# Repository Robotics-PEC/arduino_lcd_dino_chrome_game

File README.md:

# Arduino lcd dinosaur chrome game

This Repository contains a simple attempt at replicating the famous dinosaur game of Chrome and running it on an arduino with an LCD and a push button.

# Sample Pictures

## DEMO 

## This is the first screen you would see when you startup the code.

## When you press the button given then the game stars running.

## When you press the button the dinosaur jumps up.

## If you don't jump in time then you crash into the tree and game over.

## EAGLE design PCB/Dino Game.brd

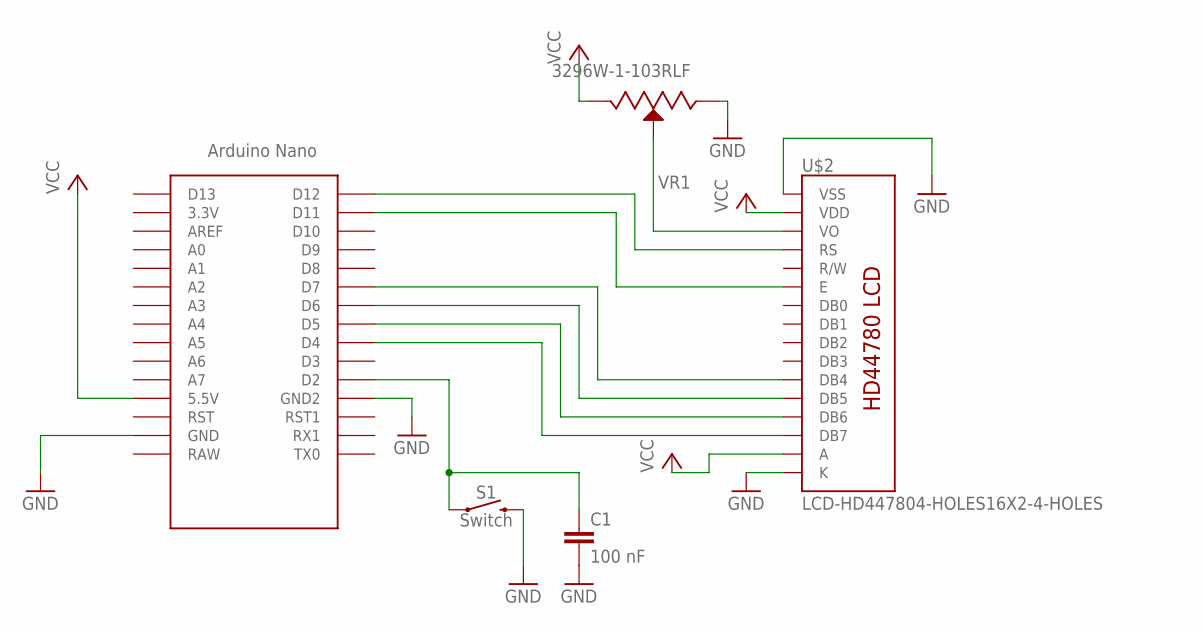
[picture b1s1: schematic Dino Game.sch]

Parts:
C1: 100 nF; C025-024X044
S1: Switch; TACTILE_SWITCH_PTH_12MM
U$1: NANO
U$2: LCD-HD447804-HOLES16X2-4-HOLES; LCD-16X2-4HOLES
VR1: 3296W-1-103RLF; TRIM_3296W-1-103RLF

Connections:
GND: C1.2, S1.3 (2), U$1.GND, U$1.GND1 (GND2), U$2.1 (VSS), U$2.16 (K), VR1.1 (CCW)
unnamed: U$1.D12, U$2.4 (RS)
unnamed: U$1.D11, U$2.6 (E)
unnamed: U$1.D7, U$2.11 (DB4)
unnamed: U$1.D6, U$2.12 (DB5)
unnamed: U$1.D5, U$2.13 (DB6)
unnamed: U$1.D4, U$2.14 (DB7)
unnamed: C1.1, S1.1, U$1.D2
unnamed: U$2.3 (VO), VR1.2 (WIPER)
VCC: U$1.5V (5.5V), U$2.2 (VDD), U$2.15 (A), VR1.3 (CW)

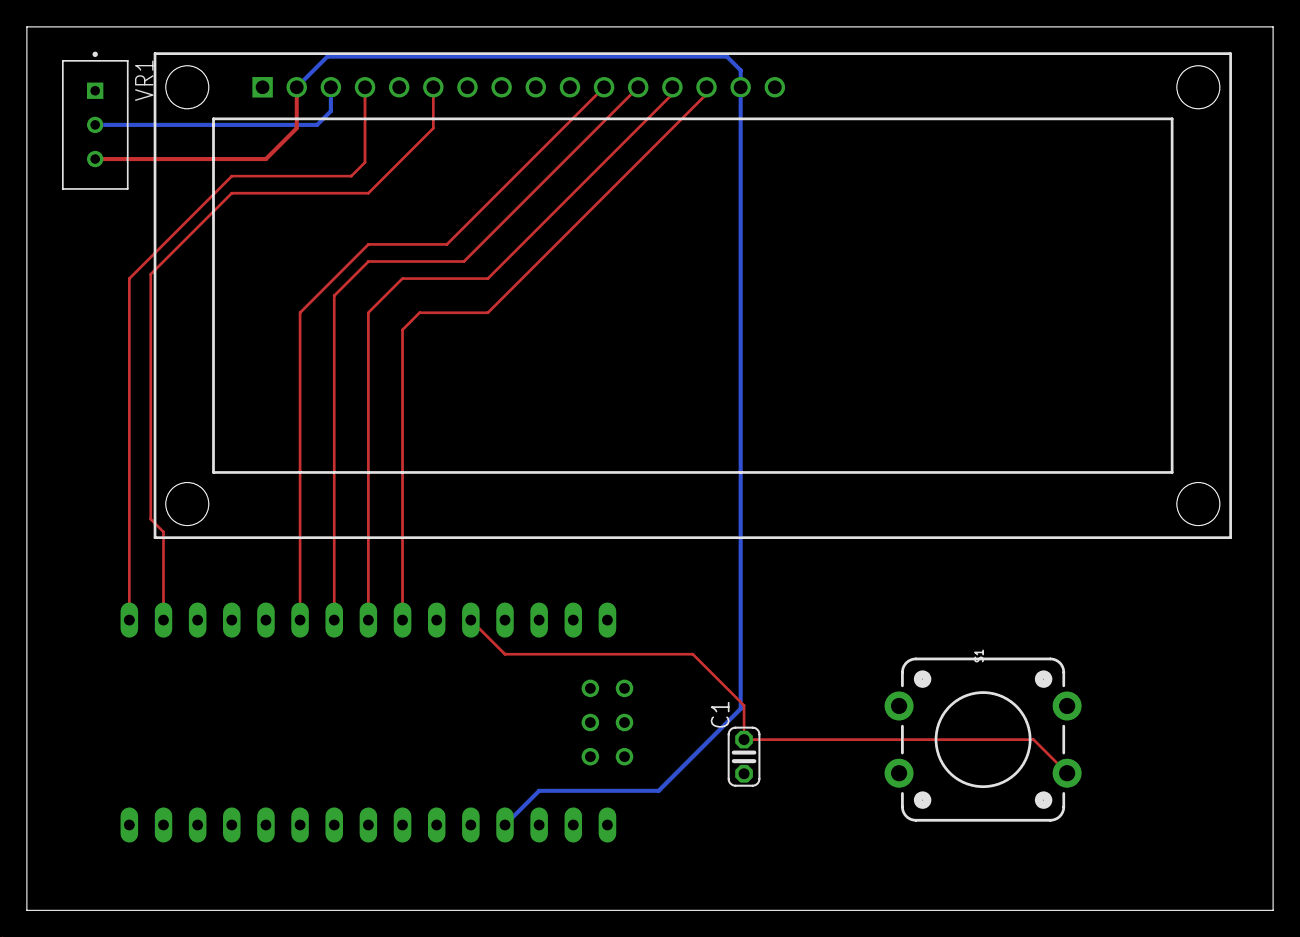
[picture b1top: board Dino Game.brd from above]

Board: 2 copper layers, 92.7 x 65.7 mm, 5 parts (0 on the bottom side), 10 nets.

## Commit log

2022-09-13 Added Readme
2022-09-13 Added Images and improved readme
2022-09-13 added animated gif to documentation
2022-09-16 Update lcd_dino_game.ino
    Added score counter and randomised the position of the tree
2022-09-18 animations
    added dino move animation and collision animation
2022-09-19 added movement animation
2022-09-22 added comments
2022-09-23 Updated comments
2022-09-25 Updated Photos
2022-10-25 added schematics and pcb files
2022-10-25 added gerber file

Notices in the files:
parts and their libraries:
SparkFun-Switches: Licensing: Creative Commons ShareAlike 4.0 International - https://creativecommons.org/licenses/by-sa/4.0
